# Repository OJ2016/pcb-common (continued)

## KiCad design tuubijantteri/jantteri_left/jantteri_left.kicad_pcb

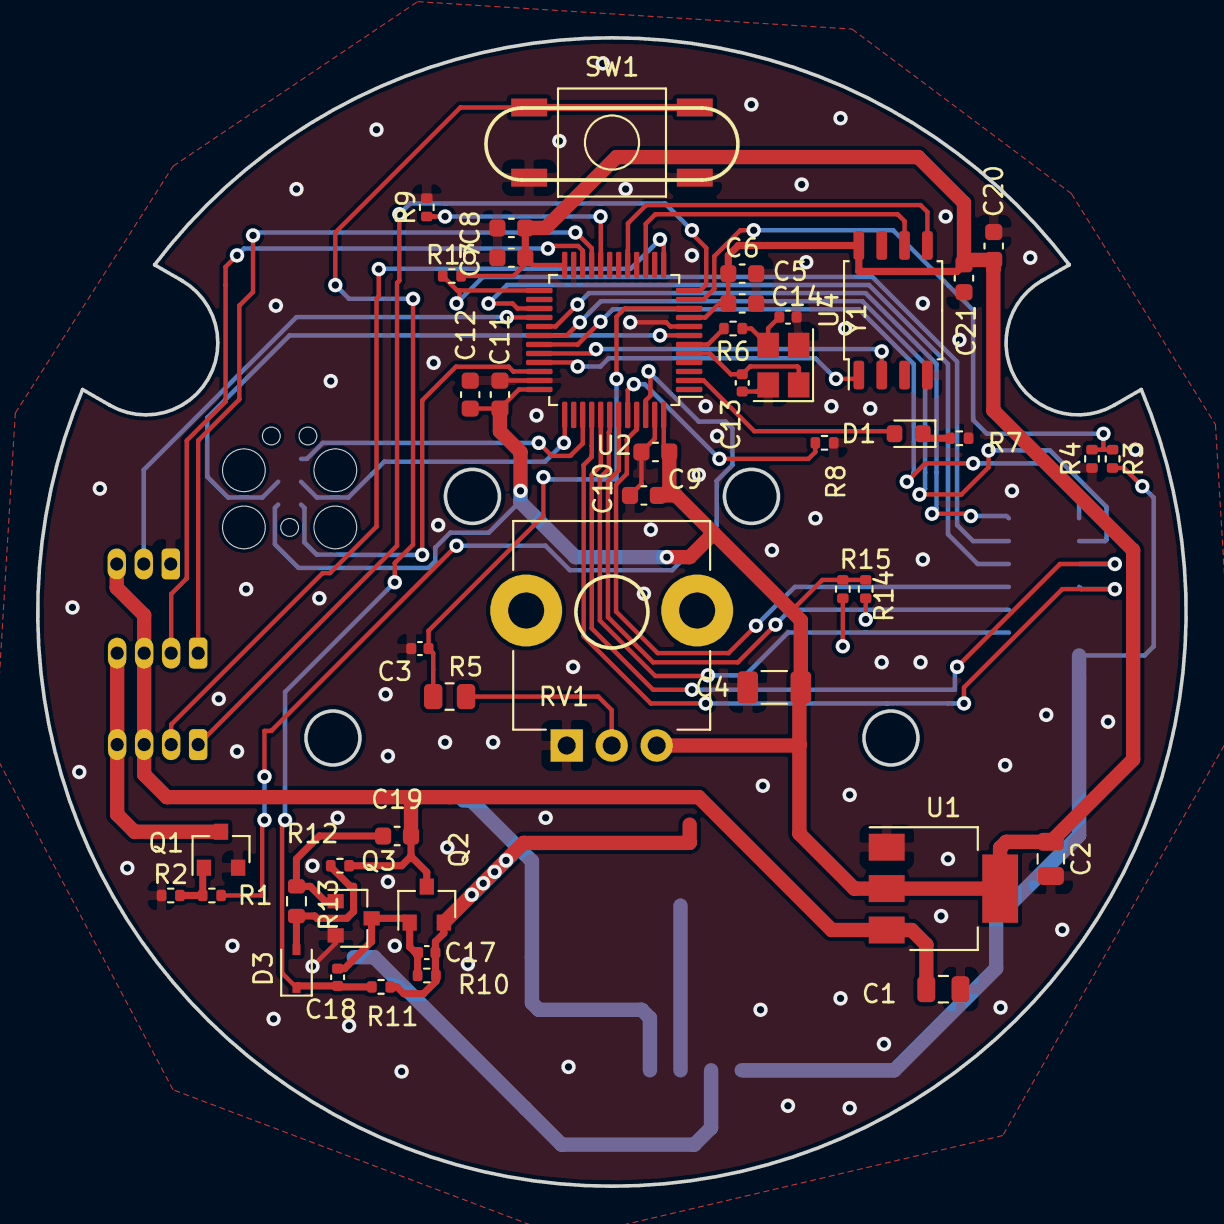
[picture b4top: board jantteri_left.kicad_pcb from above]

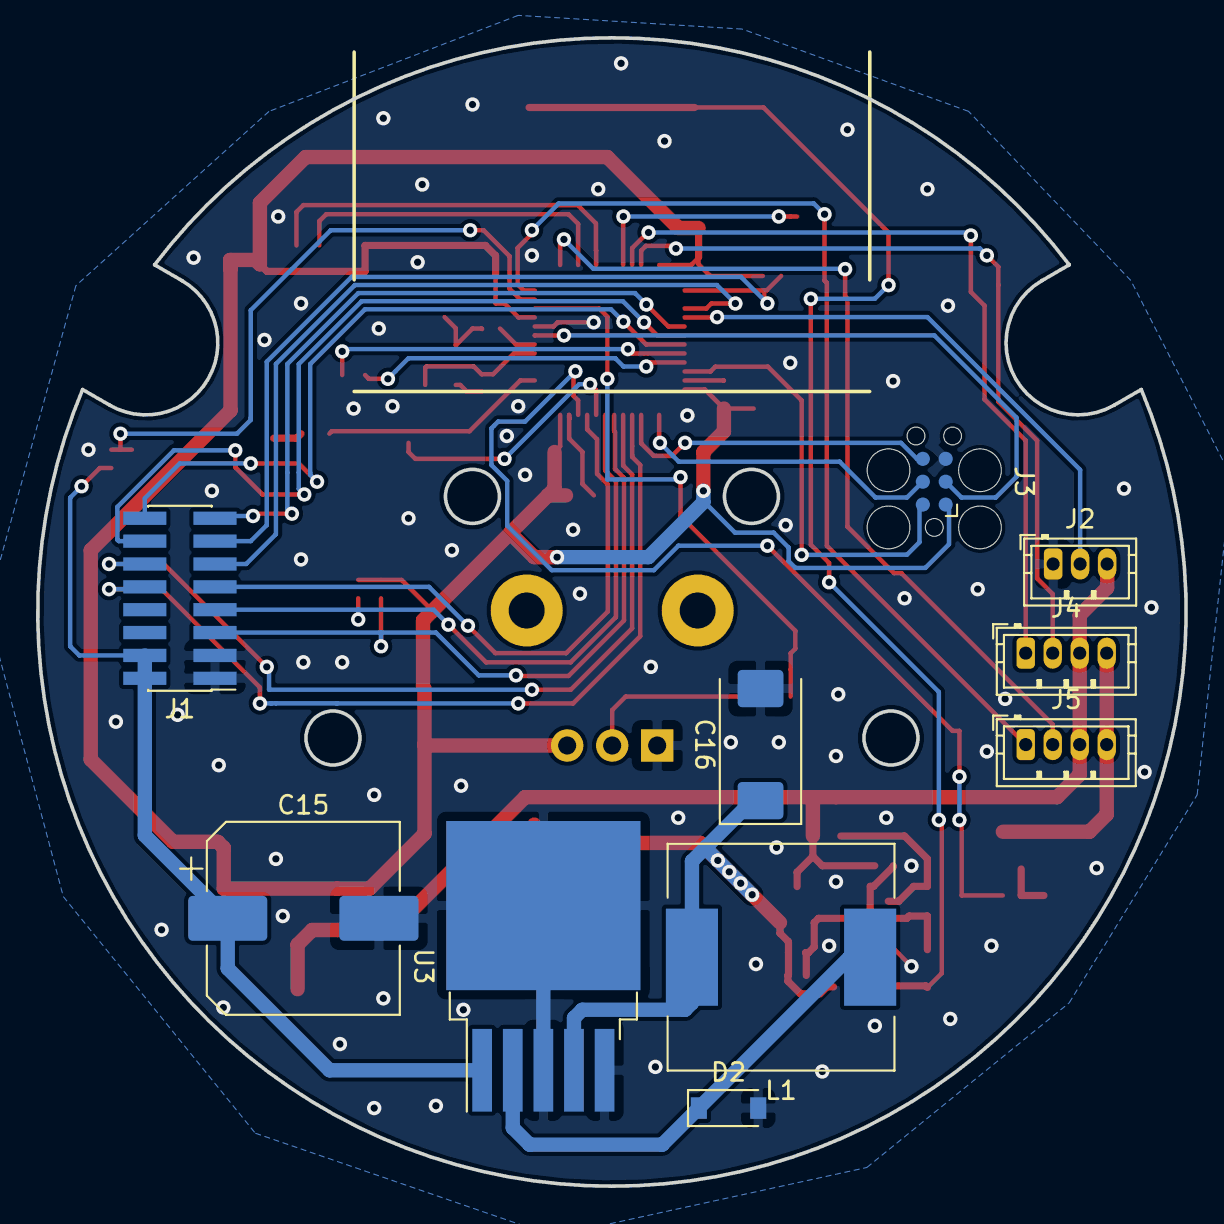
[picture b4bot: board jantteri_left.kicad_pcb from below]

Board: 2 copper layers, 63.8 x 63.8 mm, 56 parts (10 on the bottom side), 46 nets.

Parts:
C1, C2: 10u; C_0805_2012Metric
C3: 10u; C_0402_1005Metric
C4: 4u7; C_1206_3216Metric
C5, C6, C7, C8, C9, C10, C11, C12, C20, C21: 100n; C_0603_1608Metric
C13, C14: 12p; C_0402_1005Metric
C15: 680uF; CP_Elec_10x10.5
C16: 220uF; CP_EIA-7343-31_Kemet-D
C17: 0u1; C_0402_1005Metric
C18: 1u; C_0402_1005Metric
C19: 10u; C_0603_1608Metric
D1: LED; LED_0603_1608Metric
D2: SK32WA; D_SOD-123
D3: 1N5819WS; D_SOD-323
J1: Conn_02x08_Odd_Even; PinHeader_2x08_P1.27mm_Vertical_SMD
J2: Conn_01x03_Male; JST_ZH_B3B-ZR_1x03_P1.50mm_Vertical
J3: Conn_02x03_Odd_Even; Tag-Connect_TC2030-IDC-FP_2x03_P1.27mm_Vertical
J4, J5: DBG; JST_ZH_B4B-ZR_1x04_P1.50mm_Vertical
L1: 33uH; L_12x12mm_H8mm
Q1, Q3: AO3400A; SOT-23
Q2: AO3401A; SOT-23
R1: 220; R_0402_1005Metric
R2, R8, R9, R11: 10K; R_0402_1005Metric
R3: 150K; R_0402_1005Metric
R4: 20K; R_0402_1005Metric
R5: 150; R_0805_2012Metric
R6: 47; R_0402_1005Metric
R7: 1k5; R_0402_1005Metric
R10, R12: 100K; R_0402_1005Metric
R13: 300K; R_0603_1608Metric
R14, R15, R16: 4K7; R_0402_1005Metric
RV1: P0915N-FC15BR100K; Potentiometer_TT_P0915N
SW1: SW_Push; TS-1095PS-A11B3-C3D2
U1: AMS1117-3.3; SOT-223-3_TabPin2
U2: STM32L151C8TxA; LQFP-48_7x7mm_P0.5mm
U3: LM2596S-5; TO-263-5_TabPin3
U4: W25Q128JVS; SOIC-8_5.23x5.23mm_P1.27mm
Y1: 16MHz; Crystal_SMD_3225-4Pin_3.2x2.5mm

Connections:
+3V3: C2.1, C4.1, C5.1, C6.1, C7.1, C8.1, C9.1, C10.1, C11.1, C12.1, C20.1, C21.1, J3.1, R14.2, R15.2, R16.2, RV1.3, U1.2, U2.9, U2.24, U2.36, U2.48, U4.8
+5V: C1.1, C19.1, J2.3, J4.3, J5.3, Q2.3, R12.2, U1.3
/STM32L151C8T6A/BOOT0: R8.1, U2.44
/STM32L151C8T6A/BOOT1: R9.1, U2.20
/STM32L151C8T6A/HSE_IN: C13.1, U2.5, Y1.1
/STM32L151C8T6A/HSE_OUT: R6.1, U2.6
/STM32L151C8T6A/NRST: J3.3, U2.7
/STM32L151C8T6A/PA0: C3.1, R5.1, U2.10
/STM32L151C8T6A/PA2: J5.1, U2.12
/STM32L151C8T6A/PA3: J5.2, U2.13
/STM32L151C8T6A/PB10: J4.1, U2.21
/STM32L151C8T6A/PB11: J4.2, U2.22
/STM32L151C8T6A/SWCLK: J3.4, U2.37
/STM32L151C8T6A/SWDIO: J3.2, U2.34
/STM32L151C8T6A/SWO: J3.6, U2.39
/Sheet65FF0824/5V: C16.1, C17.1, L1.2, Q2.2, R10.2, R11.2, U3.4
/Sheet66006220/SW_B: C18.1, D3.1, R11.1, SW1.1
DRV_SLEEP_OUT: J1.15, U2.29
DRV_n_FAULT_OUT: J1.13, R16.1, U2.25
FLASH_CS: U2.33, U4.1
FLASH_DI: U2.17, U4.5
FLASH_DO: U2.32, U4.2
FLASH_SCK: U2.15, U4.6
GND: C1.2, C2.2, C3.2, C4.2, C5.2, C6.2, C7.2, C8.2, C9.2, C10.2, C11.2, C12.2, C13.2, C14.2, C15.2, C16.2, C20.2, C21.2, D2.2, J1.1, J1.3, J2.1, J3.5, Q1.2, Q3.2, R2.1, R4.1, R7.1, R8.2, R9.2, RV1.1, SW1.2, U1.1, U2.8, U2.23, U2.35, U2.47, U3.3, U3.5, U4.4, Y1.2, Y1.4
LED: J2.2, U2.28
MOTOR_A_OUT: J1.11, U2.27
MOTOR_B_OUT: J1.9, U2.45
unnamed: C14.1, R6.2, Y1.3
unnamed: C17.2, C18.2, Q2.1, Q3.3, R10.1
unnamed: C19.2, Q3.1, R13.2
unnamed: D1.1, R7.2
unnamed: D1.2, U2.2
unnamed: D2.1, L1.1, U3.2
unnamed: D3.2, R12.1, R13.1
unnamed: Q1.1, R1.1, R2.2
unnamed: R5.2, RV1.2
PERIPHERAL_EN: R1.2, U2.46
PERIPHERAL_GND: J4.4, J5.4, Q1.3
RXD_IN: J1.16, U2.31
SCL_IN: J1.5, R14.1, U2.42
SDA_IN: J1.7, R15.1, U2.43
STAT1_IN: J1.10, U2.40
STAT2_IN: J1.12, U2.41
TXD_IN: J1.14, U2.30
VIN_MEAS: R3.1, R4.2, U2.11
V_SYSTEM_IN: C15.1, J1.2, J1.4, R3.2, U3.1

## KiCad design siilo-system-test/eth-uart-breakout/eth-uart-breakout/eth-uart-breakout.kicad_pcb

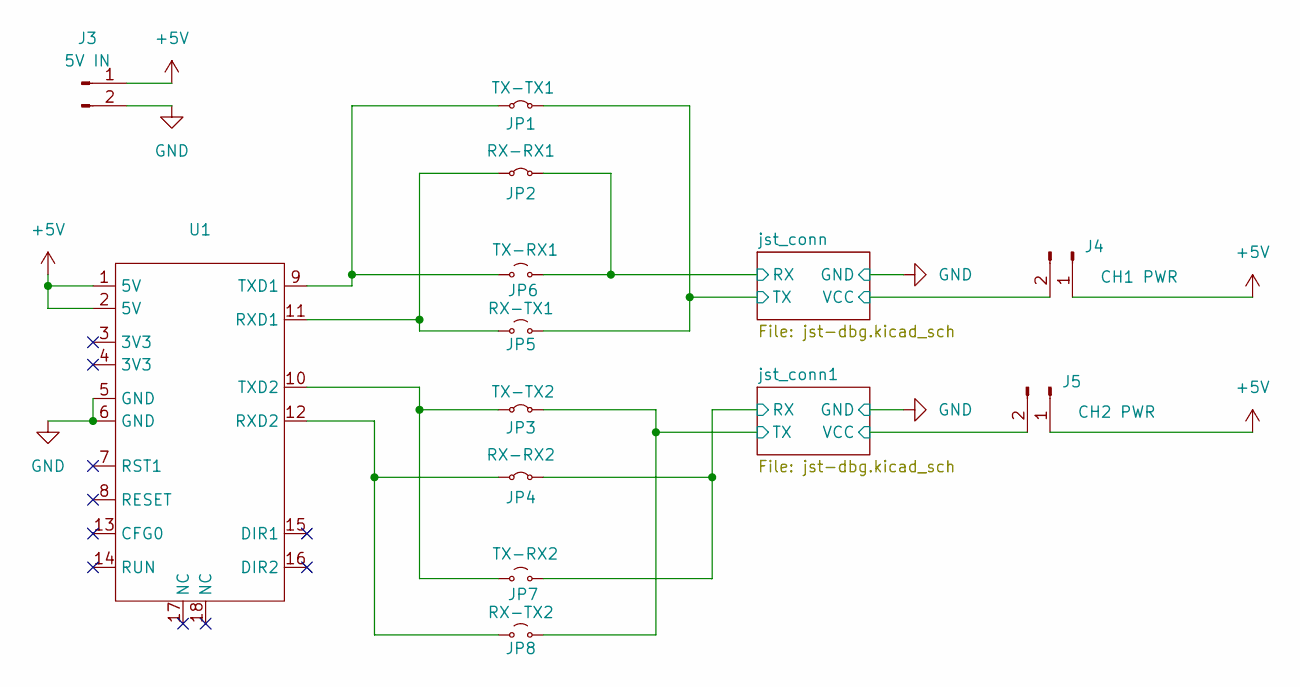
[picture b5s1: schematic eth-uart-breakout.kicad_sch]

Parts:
J3: 5V IN; TerminalBlock_bornier-2_P5.08mm
J4: CH1 PWR; TerminalBlock_bornier-2_P5.08mm
J5: CH2 PWR; TerminalBlock_bornier-2_P5.08mm
JP1: TX-TX1; SolderJumper-2_P1.3mm_Bridged_Pad1.0x1.5mm
JP2: RX-RX1; SolderJumper-2_P1.3mm_Bridged_Pad1.0x1.5mm
JP3: TX-TX2; SolderJumper-2_P1.3mm_Bridged_Pad1.0x1.5mm
JP4: RX-RX2; SolderJumper-2_P1.3mm_Bridged_Pad1.0x1.5mm
JP5: RX-TX1; SolderJumper-2_P1.3mm_Open_Pad1.0x1.5mm
JP6: TX-RX1; SolderJumper-2_P1.3mm_Open_Pad1.0x1.5mm
JP7: TX-RX2; SolderJumper-2_P1.3mm_Open_Pad1.0x1.5mm
JP8: RX-TX2; SolderJumper-2_P1.3mm_Open_Pad1.0x1.5mm
U1: WAVESHARE-2CH-UART-TO-ETH

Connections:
+5V: J3.1, J4.1, J5.1, U1.1 (5V), U1.2 (5V)
/jst_conn1/RX: JP4.2 (B), JP7.2 (B); also elsewhere on the board
/jst_conn1/TX: JP3.2 (B), JP8.2 (B); also elsewhere on the board
/jst_conn1/VCC: J5.2; also elsewhere on the board
/jst_conn/RX: JP2.2 (B), JP6.2 (B); also elsewhere on the board
/jst_conn/TX: JP1.2 (B), JP5.2 (B); also elsewhere on the board
/jst_conn/VCC: J4.2; also elsewhere on the board
GND: J3.2, U1.5 (GND), U1.6 (GND); also elsewhere on the board
unnamed: JP1.1 (A), JP6.1 (A), U1.9 (TXD1)
unnamed: JP2.1 (A), JP5.1 (A), U1.11 (RXD1)
unnamed: JP3.1 (A), JP7.1 (A), U1.10 (TXD2)
unnamed: JP4.1 (A), JP8.1 (A), U1.12 (RXD2)

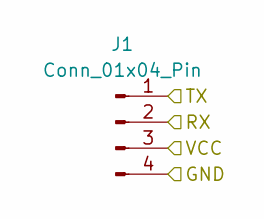
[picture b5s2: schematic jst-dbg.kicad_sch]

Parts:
J1: Conn_01x04_Pin; JST_ZH_B4B-ZR_1x04_P1.50mm_Vertical

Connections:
/jst_conn/RX: J1.2; also elsewhere on the board
/jst_conn/TX: J1.1; also elsewhere on the board
/jst_conn/VCC: J1.3; also elsewhere on the board
GND: J1.4; also elsewhere on the board

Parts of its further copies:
J2: Conn_01x04_Pin; JST_ZH_B4B-ZR_1x04_P1.50mm_Vertical

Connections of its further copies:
/jst_conn1/RX: J2.2; also elsewhere on the board
/jst_conn1/TX: J2.1; also elsewhere on the board
/jst_conn1/VCC: J2.3; also elsewhere on the board
GND: J2.4; also elsewhere on the board

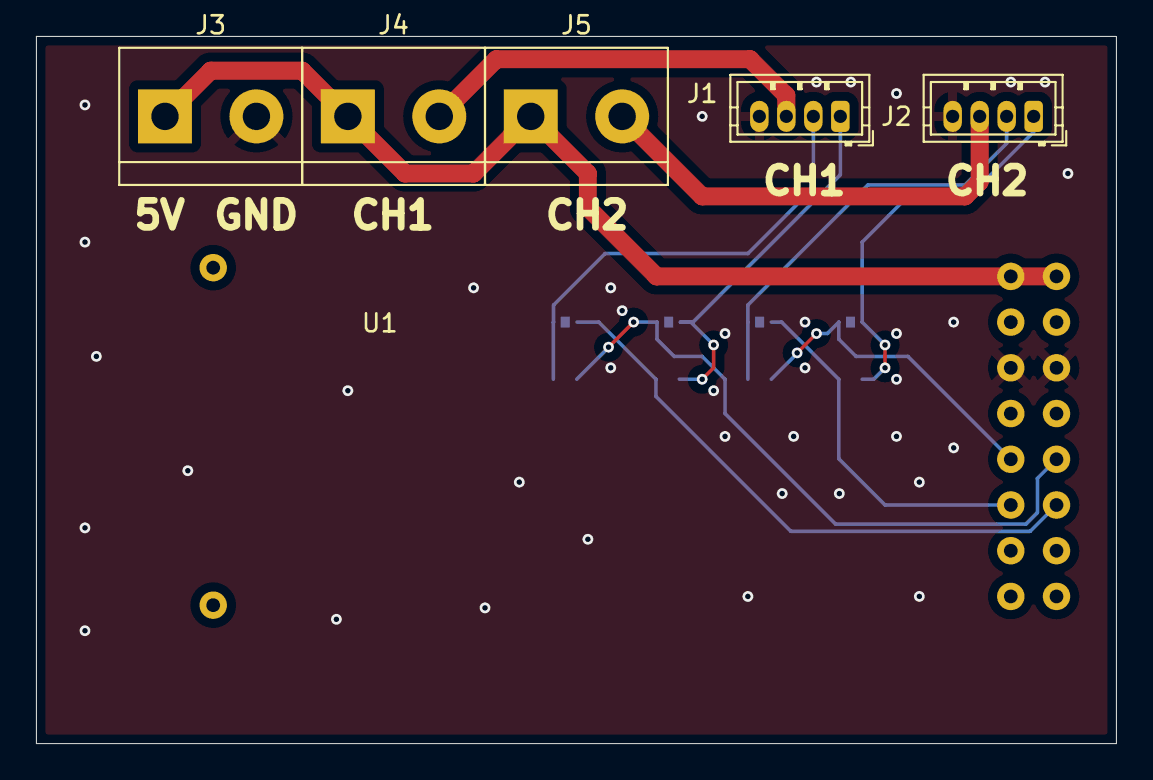
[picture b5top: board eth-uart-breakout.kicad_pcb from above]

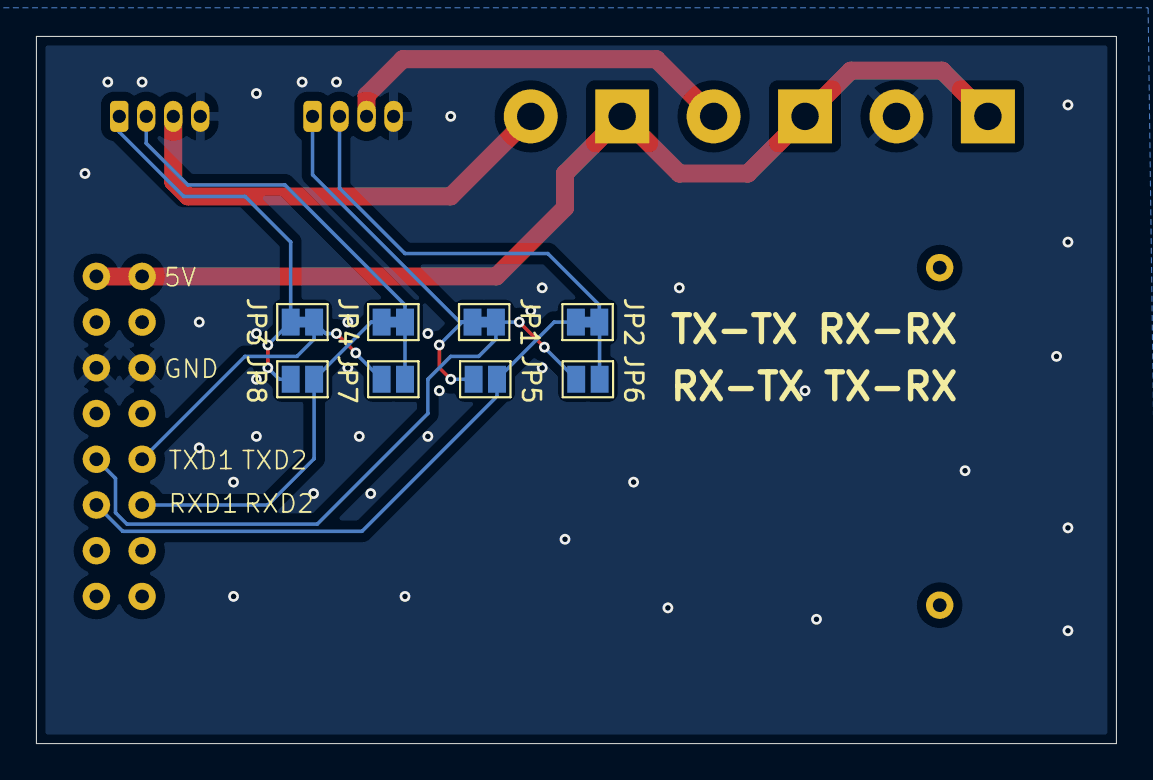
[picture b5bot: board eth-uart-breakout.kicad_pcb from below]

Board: 2 copper layers, 60.0 x 39.3 mm, 14 parts (8 on the bottom side), 12 nets.

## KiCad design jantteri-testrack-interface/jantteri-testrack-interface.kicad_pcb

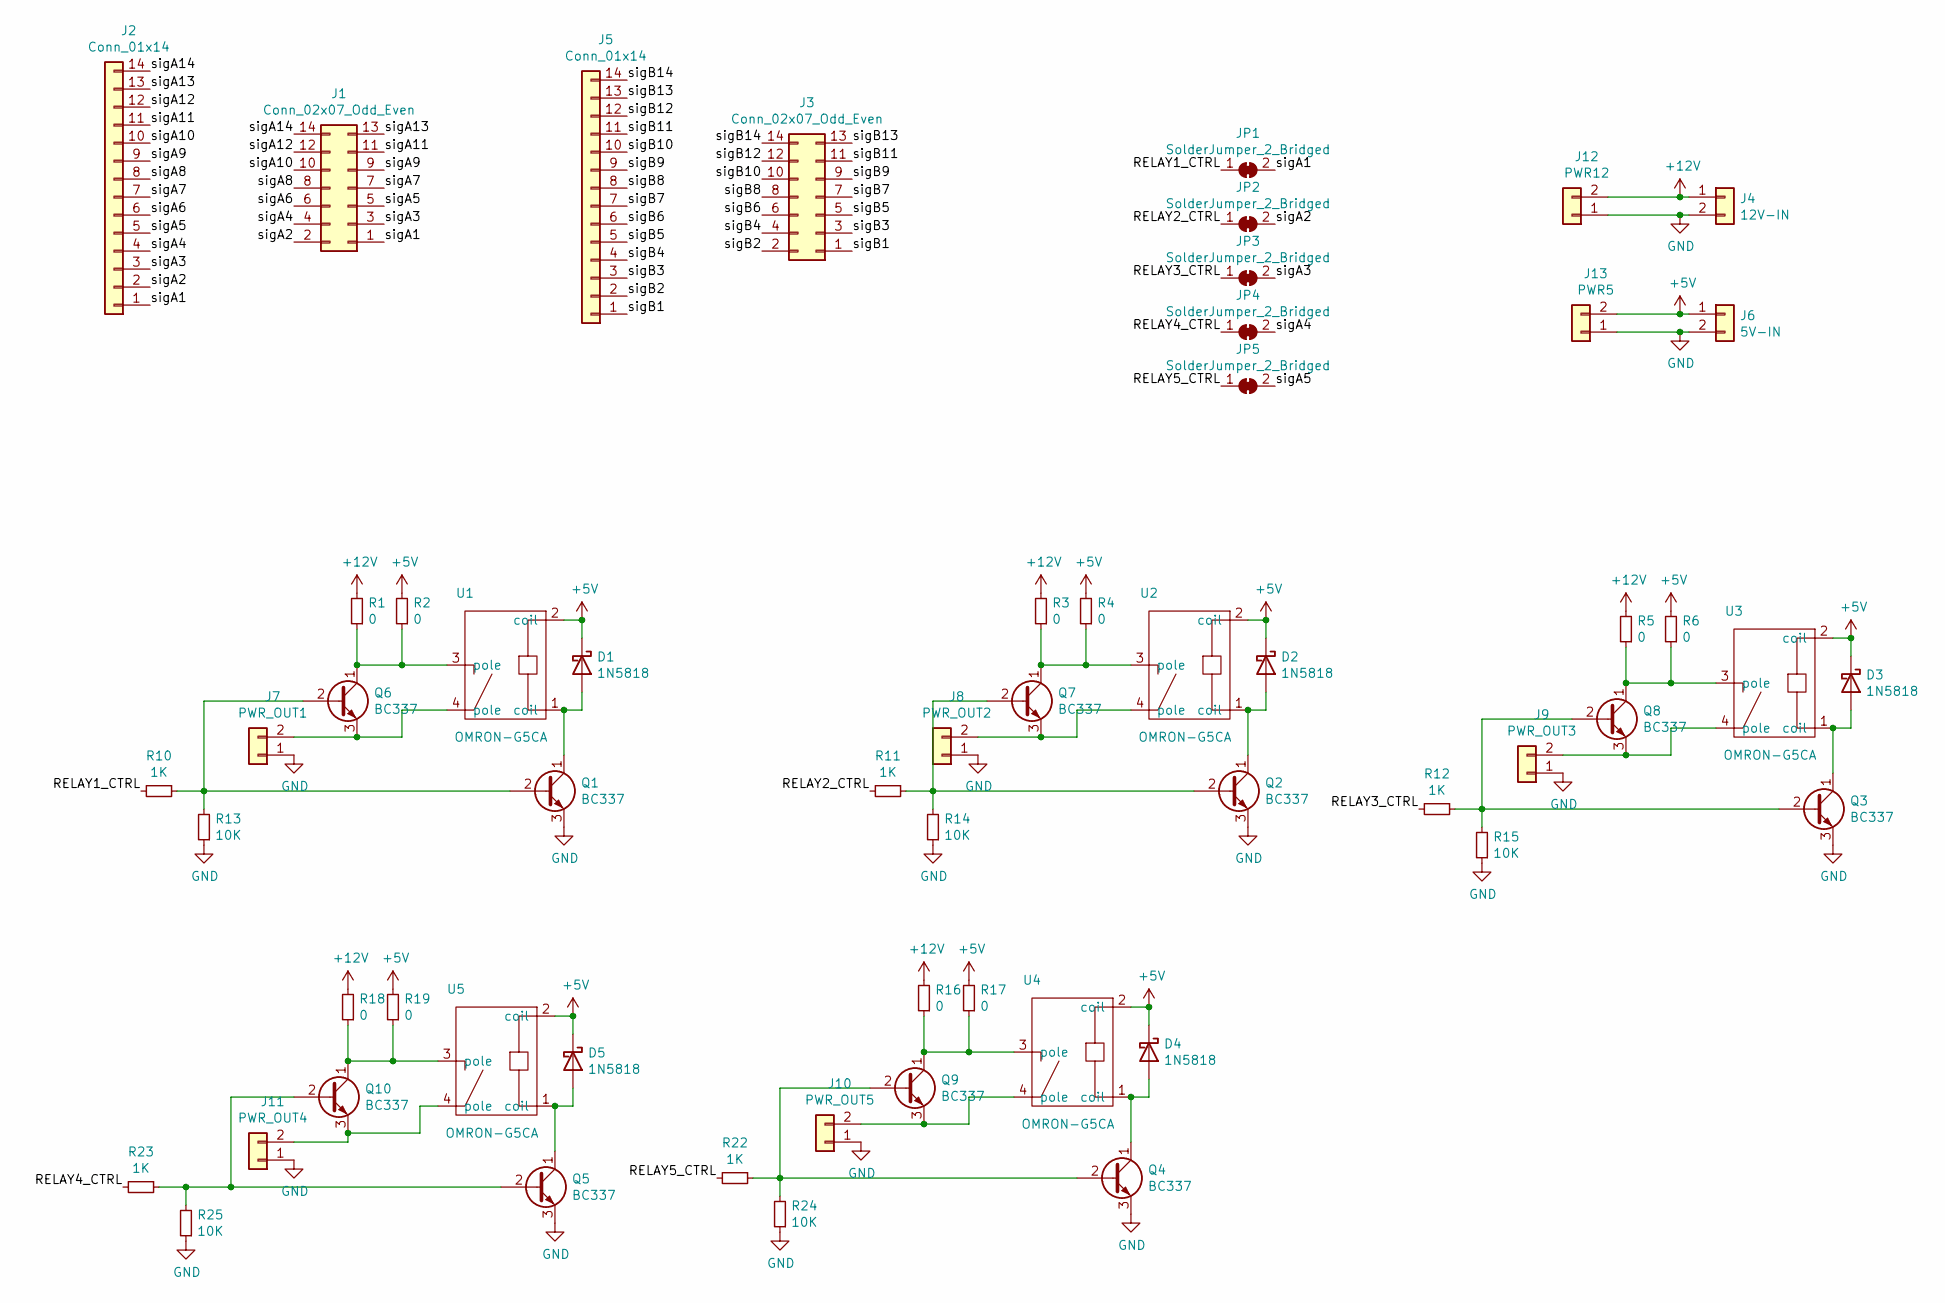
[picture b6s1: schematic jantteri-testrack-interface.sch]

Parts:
D1, D2, D3, D4, D5: 1N5818; D_DO-41_SOD81_P10.16mm_Horizontal
J1, J3: Conn_02x07_Odd_Even; PinSocket_2x07_P2.54mm_Vertical
J2, J5: Conn_01x14; PinSocket_1x14_P2.54mm_Vertical
J4: 12V-IN; terminalblock_removable_1x2
J6: 5V-IN; terminalblock_removable_1x2
J7: PWR_OUT1; TerminalBlock_bornier-2_P5.08mm
J8: PWR_OUT2; TerminalBlock_bornier-2_P5.08mm
J9: PWR_OUT3; TerminalBlock_bornier-2_P5.08mm
J10: PWR_OUT5; TerminalBlock_bornier-2_P5.08mm
J11: PWR_OUT4; TerminalBlock_bornier-2_P5.08mm
J12: PWR12; TerminalBlock_bornier-2_P5.08mm
J13: PWR5; TerminalBlock_bornier-2_P5.08mm
JP1, JP2, JP3, JP4, JP5: SolderJumper_2_Bridged; SolderJumper-2_P1.3mm_Bridged_Pad1.0x1.5mm
Q1, Q2, Q3, Q4, Q5, Q6, Q7, Q8, Q9, Q10: BC337; TO-92_Inline
R1, R2, R3, R4, R5, R6, R16, R17, R18, R19: 0; R_Axial_DIN0207_L6.3mm_D2.5mm_P7.62mm_Horizontal
R10, R11, R12, R22, R23: 1K; R_Axial_DIN0207_L6.3mm_D2.5mm_P7.62mm_Horizontal
R13, R14, R15, R24, R25: 10K; R_Axial_DIN0207_L6.3mm_D2.5mm_P7.62mm_Horizontal
U1, U2, U3, U4, U5: OMRON-G5CA

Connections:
+5V: D1.1 (K), D2.1 (K), D3.1 (K), D4.1 (K), D5.1 (K), J6.1, J13.2, R2.2, R4.2, R6.2, R17.2, R19.2, U1.2 (coil), U2.2 (coil), U3.2 (coil), U4.2 (coil), U5.2 (coil)
+12V: J4.1, J12.2, R1.2, R3.2, R5.2, R16.2, R18.2
/RELAY1_CTRL: JP1.1 (A), R10.2
/RELAY2_CTRL: JP2.1 (A), R11.2
/RELAY3_CTRL: JP3.1 (A), R12.2
/RELAY4_CTRL: JP4.1 (A), R23.2
/RELAY5_CTRL: JP5.1 (A), R22.2
/sigA1: J1.1, J2.1, JP1.2 (B)
/sigA2: J1.2, J2.2, JP2.2 (B)
/sigA3: J1.3, J2.3, JP3.2 (B)
/sigA4: J1.4, J2.4, JP4.2 (B)
/sigA5: J1.5, J2.5, JP5.2 (B)
/sigA6: J1.6, J2.6
/sigA7: J1.7, J2.7
/sigA8: J1.8, J2.8
/sigA9: J1.9, J2.9
/sigA10: J1.10, J2.10
/sigA11: J1.11, J2.11
/sigA12: J1.12, J2.12
/sigA13: J1.13, J2.13
/sigA14: J1.14, J2.14
/sigB1: J3.1, J5.1
/sigB2: J3.2, J5.2
/sigB3: J3.3, J5.3
/sigB4: J3.4, J5.4
/sigB5: J3.5, J5.5
/sigB6: J3.6, J5.6
/sigB7: J3.7, J5.7
/sigB8: J3.8, J5.8
/sigB9: J3.9, J5.9
/sigB10: J3.10, J5.10
/sigB11: J3.11, J5.11
/sigB12: J3.12, J5.12
/sigB13: J3.13, J5.13
/sigB14: J3.14, J5.14
GND: J4.2, J6.2, J7.1, J8.1, J9.1, J10.1, J11.1, J12.1, J13.1, Q1.3 (E), Q2.3 (E), Q3.3 (E), Q4.3 (E), Q5.3 (E), R13.1, R14.1, R15.1, R24.1, R25.1
unnamed: D1.2 (A), Q1.1 (C), U1.1 (coil)
unnamed: D2.2 (A), Q2.1 (C), U2.1 (coil)
unnamed: D3.2 (A), Q3.1 (C), U3.1 (coil)
unnamed: D4.2 (A), Q4.1 (C), U4.1 (coil)
unnamed: D5.2 (A), Q5.1 (C), U5.1 (coil)
unnamed: J7.2, Q6.3 (E), U1.4 (pole)
unnamed: J8.2, Q7.3 (E), U2.4 (pole)
unnamed: J9.2, Q8.3 (E), U3.4 (pole)
unnamed: J10.2, Q9.3 (E), U4.4 (pole)
unnamed: J11.2, Q10.3 (E), U5.4 (pole)
unnamed: Q1.2 (B), Q6.2 (B), R10.1, R13.2
unnamed: Q2.2 (B), Q7.2 (B), R11.1, R14.2
unnamed: Q3.2 (B), Q8.2 (B), R12.1, R15.2
unnamed: Q4.2 (B), Q9.2 (B), R22.1, R24.2
unnamed: Q6.1 (C), R1.1, R2.1, U1.3 (pole)
unnamed: Q7.1 (C), R3.1, R4.1, U2.3 (pole)
unnamed: Q8.1 (C), R5.1, R6.1, U3.3 (pole)
unnamed: Q9.1 (C), R16.1, R17.1, U4.3 (pole)
unnamed: Q10.1 (C), R18.1, R19.1, U5.3 (pole)
unnamed: Q5.2 (B), Q10.2 (B), R23.1, R25.2

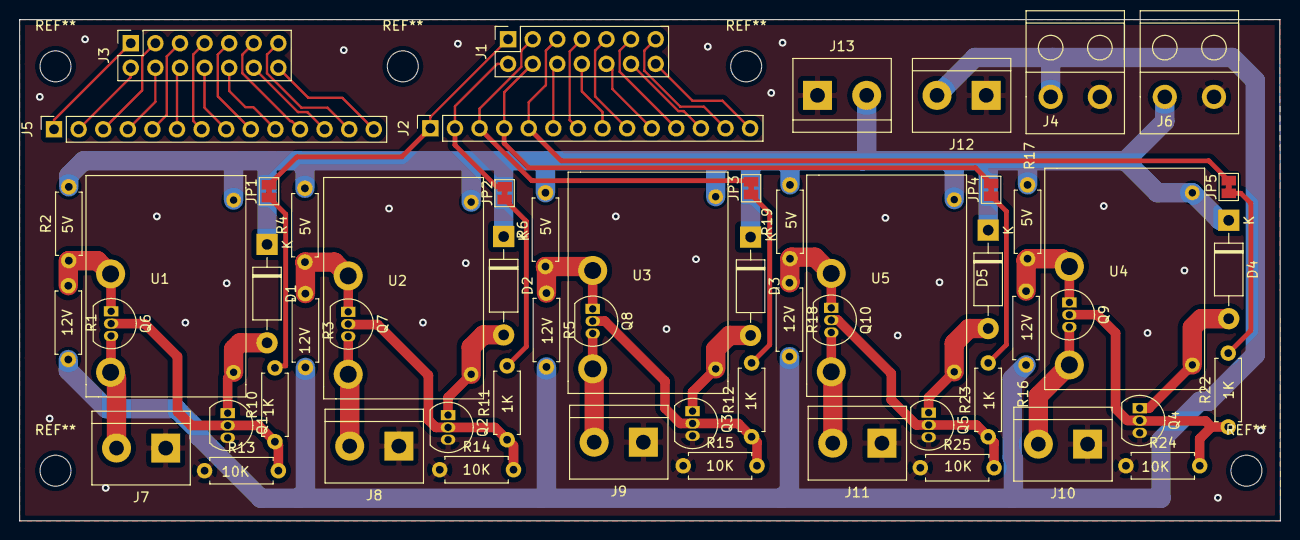
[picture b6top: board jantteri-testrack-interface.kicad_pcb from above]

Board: 2 copper layers, 130.2 x 51.8 mm, 58 parts (0 on the bottom side), 56 nets.

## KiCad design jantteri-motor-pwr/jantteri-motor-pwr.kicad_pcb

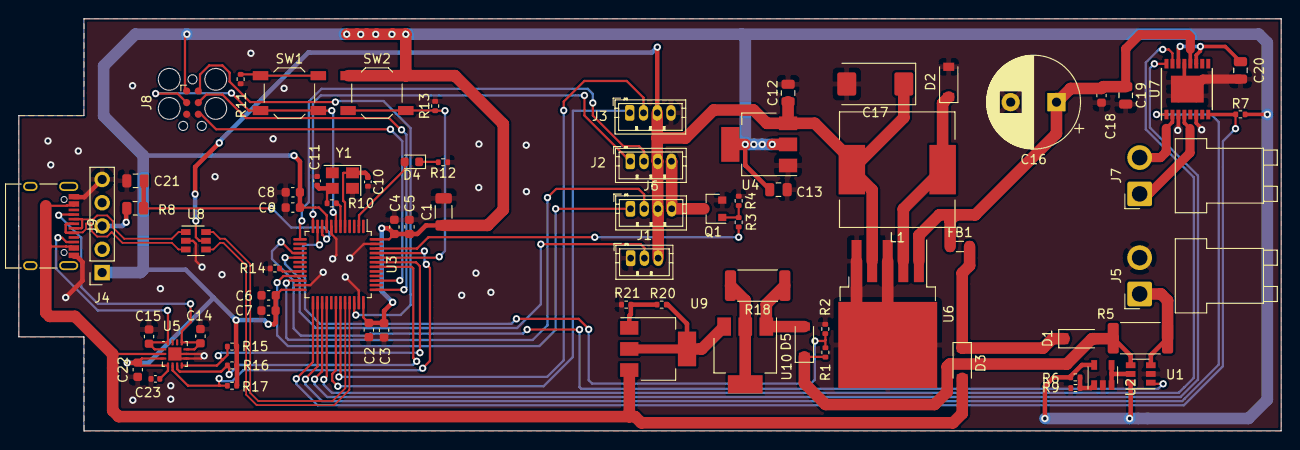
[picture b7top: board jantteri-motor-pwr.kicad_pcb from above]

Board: 2 copper layers, 137.7 x 45.0 mm, 73 parts (0 on the bottom side), 57 nets.

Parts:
C1: 4u7; C_1206_3216Metric
C2, C3, C4, C5, C6, C7, C8, C9, C18, C22: 100n; C_0603_1608Metric
C10, C11: 12p; C_0402_1005Metric
C12, C13, C19, C21: 10u; C_0805_2012Metric
C14, C15: 400p; C_0603_1608Metric
C16: 680uF; CP_Radial_D10.0mm_P5.00mm
C17: 220uF; CP_EIA-7343-31_Kemet-D
C20: 2u2; C_0805_2012Metric
C23: 1u; C_0402_1005Metric
D1, D3, D5: B5819W SL; D_SOD-123
D2: SK32WA; D_SOD-123
D4: LED; LED_0603_1608Metric
FB1: GZ2012D101TF; L_0805_2012Metric
J1: LED; JST_ZH_B3B-ZR_1x03_P1.50mm_Vertical
J2, J3, J6: DBG; JST_ZH_B4B-ZR_1x04_P1.50mm_Vertical
J4: Conn_01x05; PinSocket_1x05_P2.54mm_Vertical
J5: BAT; JST_VH_B2PS-VH_1x02_P3.96mm_Horizontal
J7: M; JST_VH_B2PS-VH_1x02_P3.96mm_Horizontal
J8: Conn_02x03_Odd_Even; Tag-Connect_TC2030-IDC-FP_2x03_P1.27mm_Vertical
J9: USB_C_Receptacle_USB2.0; USB_C_Receptacle_XKB_U262-16XN-4BVC11
L1: 33uH; L_12x12mm_H8mm
Q1: AO3400A; SOT-23
R1: 150K; R_0402_1005Metric
R2: 15K; R_0402_1005Metric
R3, R20: 220; R_0402_1005Metric
R4, R7, R11, R13, R14: 10K; R_0402_1005Metric
R5: R510; R_2512_6332Metric
R6, R9: 100K; R_0402_1005Metric
R8: 150; R_0805_2012Metric
R10: 47; R_0402_1005Metric
R12: 1k5; R_0402_1005Metric
R15, R16, R17: 4K7; R_0402_1005Metric
R18: 5R1; R_2512_6332Metric
R21: 2K4; R_0402_1005Metric
SW1, SW2: SW_SPST; SW_SPST_TL3342
U1: INA181; SOT-23-6
U2: LMV321; SOT-23-5
U3: STM32L151C8TxA; LQFP-48_7x7mm_P0.5mm
U4: AMS1117-3.3; SOT-223-3_TabPin2
U5: FUSB302BMPX; WQFN-14-1EP_2.5x2.5mm_P0.5mm_EP1.45x1.45mm
U6: LM2596S-5; TO-263-5_TabPin3
U7: DRV8848; TSSOP-16-1EP_4.4x5mm_P0.65mm
U8: USBLC6-2SC6; SOT-23-6
U9, U10: LM317_SOT-223; SOT-223-3_TabPin2
Y1: 16MHz; Crystal_SMD_3225-4Pin_3.2x2.5mm

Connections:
+3V3: C1.1, C2.1, C3.1, C4.1, C5.1, C6.1, C7.1, C8.1, C9.1, C13.1, C22.1, C23.1, J4.1, J8.1, R6.2, R7.2, R15.1, R16.1, R17.1, SW2.1, U1.6, U2.5, U3.9, U3.24, U3.36, U3.48, U4.2, U5.3, U5.4
+5V: C12.1, C17.1, J1.3, J2.3, J3.3, J6.3, L1.2, U4.3, U6.4, U8.5
/DRV8848/VINT: C20.2, U7.11, U7.14
/STM32L151C8T6A/BOOT0: R13.1, SW2.2, U3.44
/STM32L151C8T6A/BOOT1: R14.1, U3.20
/STM32L151C8T6A/HSE_IN: C10.1, U3.5, Y1.1
/STM32L151C8T6A/HSE_OUT: R10.1, U3.6
/STM32L151C8T6A/NRST: J8.3, SW1.2, U3.7
/STM32L151C8T6A/PA2: J2.1, U3.12
/STM32L151C8T6A/PA3: J2.2, U3.13
/STM32L151C8T6A/PA9: J3.1, U3.30
/STM32L151C8T6A/PA10: J3.2, U3.31
/STM32L151C8T6A/PB10: J6.1, U3.21
/STM32L151C8T6A/PB11: J6.2, U3.22
/STM32L151C8T6A/SWCLK: J8.4, U3.37
/STM32L151C8T6A/SWDIO: J8.2, U3.34
/STM32L151C8T6A/SWO: J8.6, U3.39
/usbc/CC1: C14.1, J9.A5, U5.10, U5.11
/usbc/CC2: C15.1, J9.B5, U5.1, U5.14
/usbc/USB_CONN_D+: J9.A6, J9.B6, U8.3
/usbc/USB_CONN_D-: J9.A7, J9.B7, U8.1
BAT+: D1.2, D5.1, R1.2, R5.2, U1.4
BATMEAS: R1.1, R2.2, U3.11
CURMEAS: U1.1, U3.16
DRV_FAULT: R7.1, U3.25, U7.8
DRV_SLEEP: U3.26, U7.1
GND: C1.2, C2.2, C3.2, C4.2, C5.2, C6.2, C7.2, C8.2, C9.2, C10.2, C11.2, C12.2, C13.2, C14.2, C15.2, C16.2, C17.2, C18.2, C19.2, C20.1, C21.2, C22.2, C23.2, D2.2, J1.1, J3.4, J4.5, J5.2, J8.5, J9.A1, J9.A12, J9.B1, J9.B12, Q1.2, R2.1, R4.1, R9.1, R11.2, R12.1, R13.2, R14.2, R21.2, U1.2, U2.2, U3.8, U3.23, U3.35, U3.47, U4.1, U5.8, U5.9, U5.15, U6.3, U6.5, U7.3, U7.6, U7.13, U7.17, U8.2, Y1.2, Y1.4
LED: J1.2, U3.17
M+: J7.1, U7.4
M-: J7.2, U7.2
MOTOR_A: U3.27, U7.16
MOTOR_B: U3.28, U7.15
unnamed: C11.1, R10.2, Y1.3
unnamed: D1.1, D3.1, FB1.2
unnamed: D2.1, L1.1, U6.2
unnamed: D4.1, R12.2
unnamed: D4.2, U3.2
unnamed: D5.2, R18.1, U10.1
unnamed: J4.3, R8.2
unnamed: J5.1, R5.1, U1.3
unnamed: Q1.1, R3.2, R4.2
unnamed: R6.1, R9.2, U2.1
unnamed: R11.1, SW1.1
unnamed: R18.2, U10.2
unnamed: R20.1, U9.2, U10.3
unnamed: R20.2, R21.1, U9.1
unnamed: U1.5, U2.3, U2.4
PERIPH_EN: R3.1, U3.46
PERIPH_GND: J2.4, J6.4, Q1.3
POT: C21.1, R8.1, U3.10
USB_D+: U3.33, U8.4
USB_D-: U3.32, U8.6
USB_INT: R17.2, U3.45, U5.5
USB_SCL: R16.2, U3.42, U5.6
USB_SDA: R15.2, U3.43, U5.7
VBUS: D3.2, J9.A4, J9.A9, J9.B4, J9.B9, U5.2, U9.3
VIN: C16.1, C18.1, C19.1, FB1.1, U6.1, U7.12

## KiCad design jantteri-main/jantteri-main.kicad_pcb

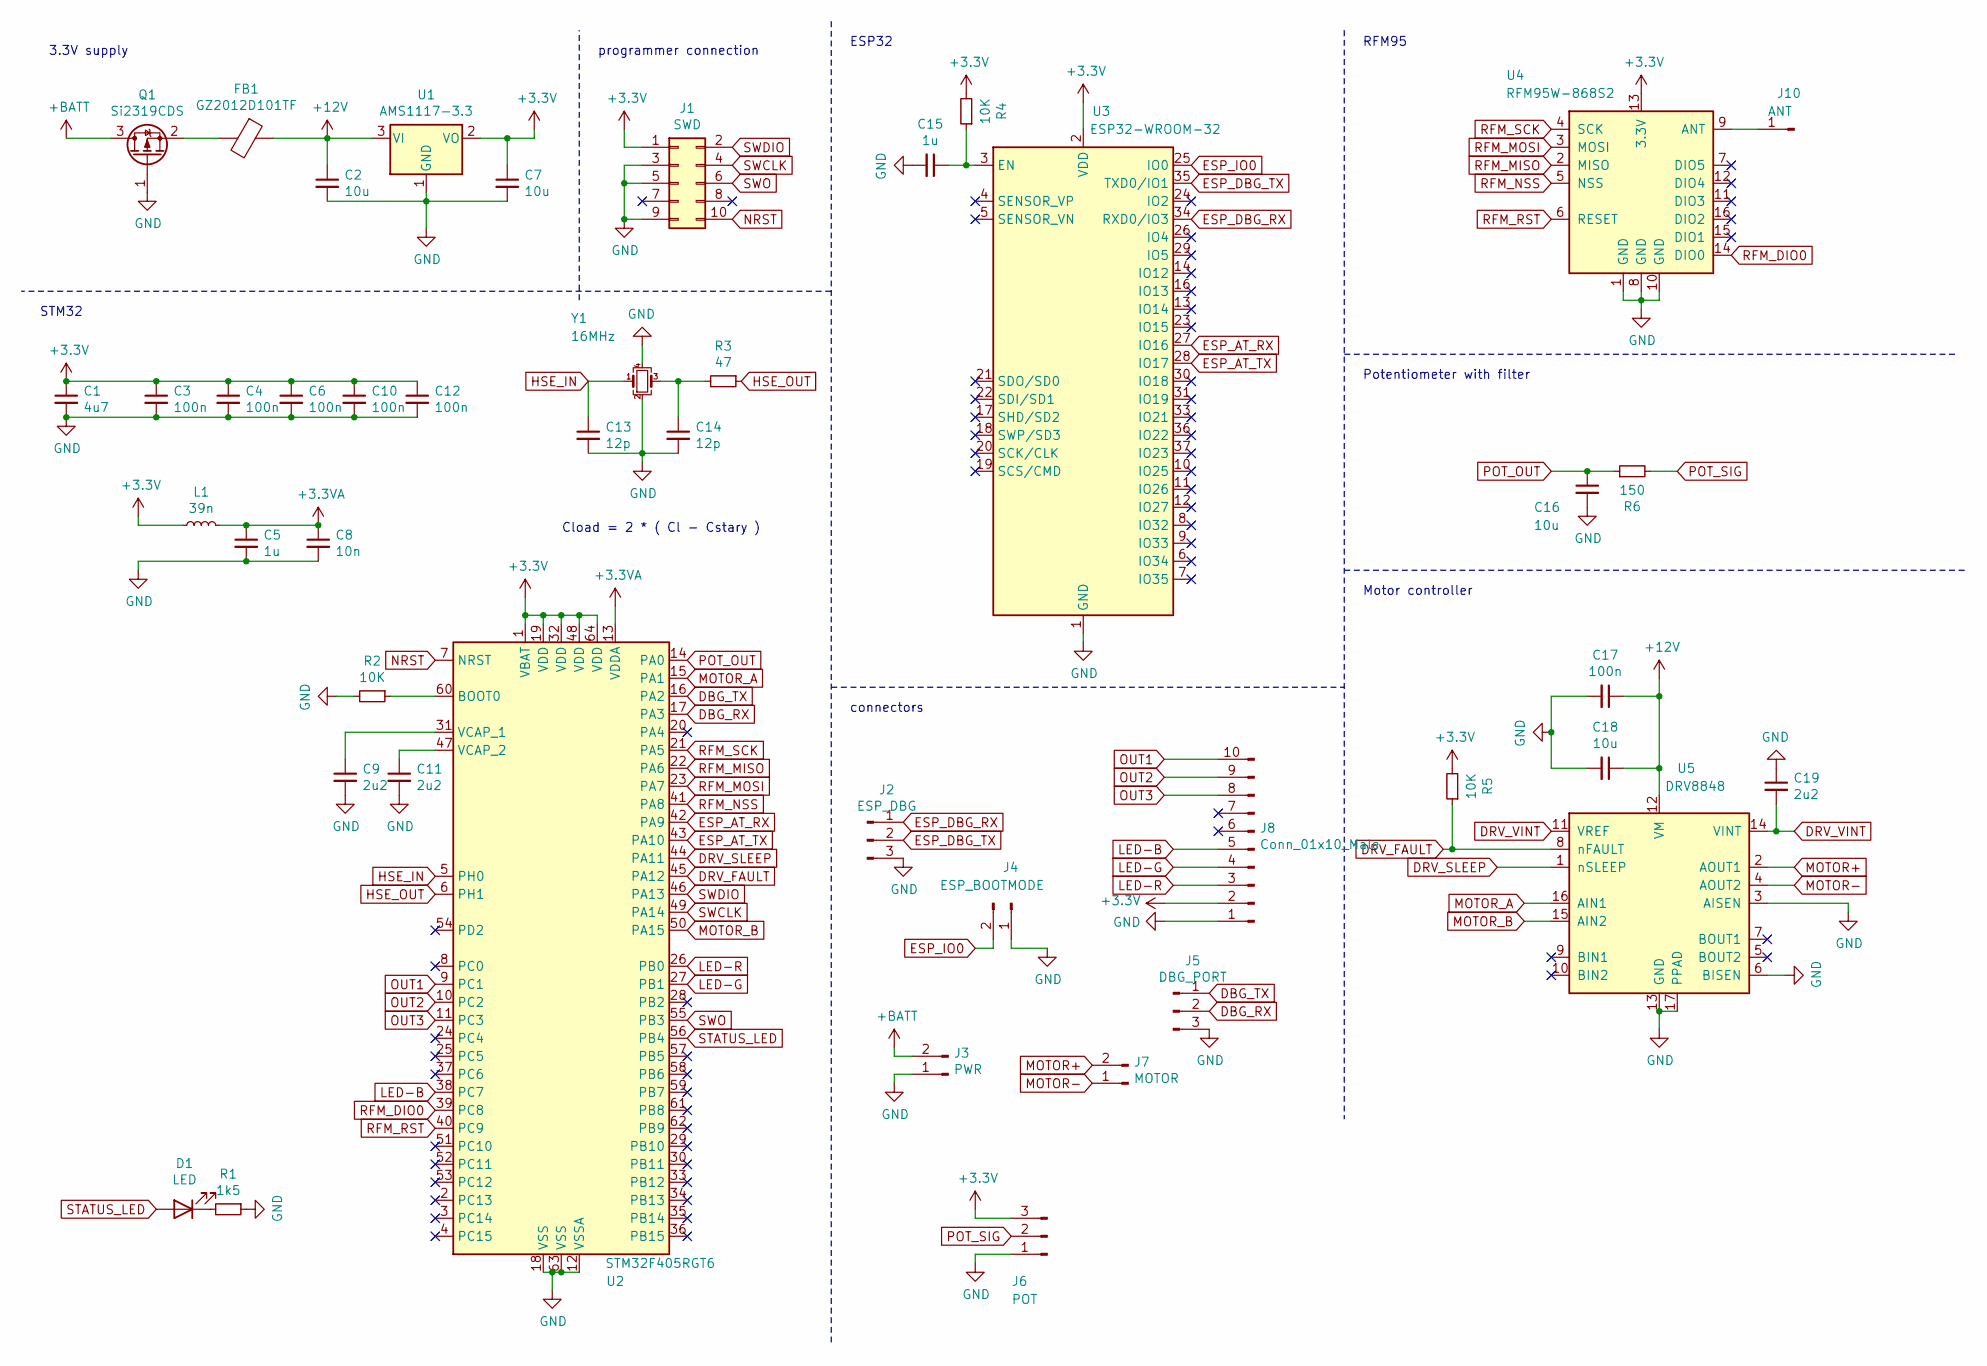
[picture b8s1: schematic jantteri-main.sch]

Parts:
C1: 4u7; C_1206_3216Metric; LCSC C29823
C2, C7, C16, C18: 10u; C_0805_2012Metric; LCSC C15850
C3, C4, C6, C10, C12, C17: 100n; C_0603_1608Metric; LCSC C14663
C5, C15: 1u; C_0805_2012Metric; LCSC C28323
C8: 10n; C_0805_2012Metric; LCSC C1710
C9, C11, C19: 2u2; C_0805_2012Metric; LCSC C49217
C13, C14: 12p; C_0402_1005Metric; LCSC C1547
D1: LED; LED_0603_1608Metric; LCSC C72041
FB1: GZ2012D101TF; L_0805_2012Metric; LCSC C1015
J1: SWD; PinHeader_2x05_P1.27mm_Vertical_SMD
J2: ESP_DBG; JST_ZH_B3B-ZR_1x03_P1.50mm_Vertical
J3: PWR; JST_ZH_B2B-ZR_1x02_P1.50mm_Vertical
J4: ESP_BOOTMODE; PinHeader_1x02_P2.54mm_Vertical
J5: DBG_PORT; JST_ZH_B3B-ZR_1x03_P1.50mm_Vertical
J6: POT; JST_ZH_B3B-ZR_1x03_P1.50mm_Vertical
J7: MOTOR; JST_ZH_B2B-ZR_1x02_P1.50mm_Vertical
J8: Conn_01x10_Male; JST_ZH_B10B-ZR_1x10_P1.50mm_Vertical
J10: ANT; PinHeader_1x01_P2.54mm_Vertical
L1: 39n; L_0402_1005Metric; LCSC C26443
Q1: Si2319CDS; SOT-23; LCSC C146287
R1: 1k5; R_0402_1005Metric; LCSC C25867
R2, R4, R5: 10K; R_0402_1005Metric; LCSC C25744
R3: 47; R_0402_1005Metric; LCSC C25118
R6: 150; R_0805_2012Metric; LCSC C17471
U1: AMS1117-3.3; SOT-223-3_TabPin2; LCSC C6186
U2: STM32F405RGT6; LQFP-64_10x10mm_P0.5mm; LCSC C15742
U3: ESP32-WROOM-32
U4: RFM95W-868S2; HOPERF_RFM9XW_SMD
U5: DRV8848; TSSOP-16-1EP_4.4x5mm_P0.65mm; LCSC C131079
Y1: 16MHz; Crystal_SMD_3225-4Pin_3.2x2.5mm; LCSC C13738

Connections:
+3.3VA: C5.1, C8.1, L1.2, U2.13 (VDDA)
+3V3: C1.1, C3.1, C4.1, C6.1, C7.1, C10.1, C12.1, J1.1, J6.3, J8.2, L1.1, R4.2, R5.2, U1.2 (VO), U2.1 (VBAT), U2.19 (VDD), U2.32 (VDD), U2.48 (VDD), U2.64 (VDD), U3.2 (VDD), U4.13 (3.3V)
+12V: C2.1, C17.1, C18.1, FB1.1, U1.3 (VI), U5.12 (VM)
+BATT: J3.2, Q1.3 (D)
DBG_RX: J5.2, U2.17 (PA3)
DBG_TX: J5.1, U2.16 (PA2)
DRV_FAULT: R5.1, U2.45 (PA12), U5.8 (nFAULT)
DRV_SLEEP: U2.44 (PA11), U5.1 (nSLEEP)
DRV_VINT: C19.2, U5.11 (VREF), U5.14 (VINT)
ESP_AT_RX: U2.42 (PA9), U3.27 (IO16)
ESP_AT_TX: U2.43 (PA10), U3.28 (IO17)
ESP_DBG_RX: J2.1, U3.34 (RXD0/IO3)
ESP_DBG_TX: J2.2, U3.35 (TXD0/IO1)
ESP_IO0: J4.2, U3.25 (IO0)
GND: C1.2, C2.2, C3.2, C4.2, C5.2, C6.2, C7.2, C8.2, C9.2, C10.2, C11.2, C12.2, C13.2, C14.2, C15.2, C16.2, C17.2, C18.2, C19.1, J1.3, J1.5, J1.9, J2.3, J3.1, J4.1, J5.3, J6.1, J8.1, Q1.1 (G), R1.1, R2.2, U1.1 (GND), U2.12 (VSSA), U2.18 (VSS), U2.63 (VSS), U3.1 (GND), U3.15 (GND), U3.38 (GND), U3.39 (GND), U4.1 (GND), U4.8 (GND), U4.10 (GND), U5.3 (AISEN), U5.6 (BISEN), U5.13 (GND), U5.17 (PPAD), Y1.2, Y1.4
HSE_IN: C13.1, U2.5 (PH0), Y1.1
HSE_OUT: R3.1, U2.6 (PH1)
LED-B: J8.5, U2.38 (PC7)
LED-G: J8.4, U2.27 (PB1)
LED-R: J8.3, U2.26 (PB0)
MOTOR+: J7.2, U5.2 (AOUT1)
MOTOR-: J7.1, U5.4 (AOUT2)
MOTOR_A: U2.15 (PA1), U5.16 (AIN1)
MOTOR_B: U2.50 (PA15), U5.15 (AIN2)
NRST: J1.10, U2.7 (NRST)
unnamed: C9.1, U2.31 (VCAP_1)
unnamed: C11.1, U2.47 (VCAP_2)
unnamed: C14.1, R3.2, Y1.3
unnamed: C15.1, R4.1, U3.3 (EN)
unnamed: D1.1 (K), R1.2
unnamed: FB1.2, Q1.2 (S)
unnamed: J10.1, U4.9 (ANT)
unnamed: R2.1, U2.60 (BOOT0)
OUT1: J8.10, U2.9 (PC1)
OUT2: J8.9, U2.10 (PC2)
OUT3: J8.8, U2.11 (PC3)
POT_OUT: C16.1, R6.1, U2.14 (PA0)
POT_SIG: J6.2, R6.2
RFM_DIO0: U2.39 (PC8), U4.14 (DIO0)
RFM_MISO: U2.22 (PA6), U4.2 (MISO)
RFM_MOSI: U2.23 (PA7), U4.3 (MOSI)
RFM_NSS: U2.41 (PA8), U4.5 (NSS)
RFM_RST: U2.40 (PC9), U4.6 (RESET)
RFM_SCK: U2.21 (PA5), U4.4 (SCK)
STATUS_LED: D1.2 (A), U2.56 (PB4)
SWCLK: J1.4, U2.49 (PA14)
SWDIO: J1.2, U2.46 (PA13)
SWO: J1.6, U2.55 (PB3)

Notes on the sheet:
Cload = 2 * ( Cl - Cstary )
3.3V supply
programmer connection
STM32
ESP32
RFM95
connectors
Motor controller
Potentiometer with filter
